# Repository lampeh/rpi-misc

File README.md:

rpi-misc
========

Raspberry Pi Gefrickel

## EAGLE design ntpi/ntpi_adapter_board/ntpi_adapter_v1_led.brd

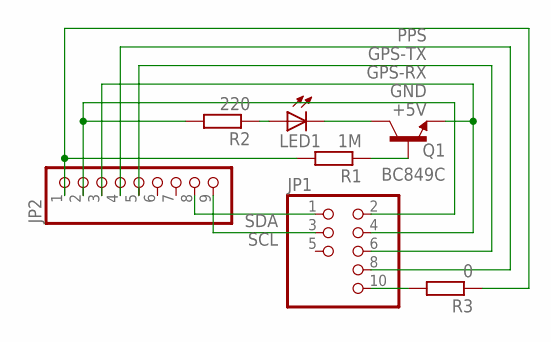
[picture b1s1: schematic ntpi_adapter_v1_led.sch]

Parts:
JP1: PINHEAD-NTPI
JP2: PINHD-1X9; 1X09
LED1: LEDCHIPLED_0805; CHIPLED_0805
Q1: BC849C; SOT23
R1: 1M; R0805W
R2: 220; R0805W
R3: 0; R0805W

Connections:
+5V: JP1.2, JP2.2, R2.2
GND: JP1.4, JP2.3, Q1.2 (E)
GPS-RX: JP1.6, JP2.5
GPS-TX: JP1.8, JP2.4
unnamed: JP1.10, R3.2
unnamed: LED1.A, R2.1
unnamed: LED1.C, Q1.3 (C)
unnamed: Q1.1 (B), R1.1
PPS: JP2.1, R1.2, R3.1
SCL: JP1.3, JP2.9
SDA: JP1.1, JP2.8

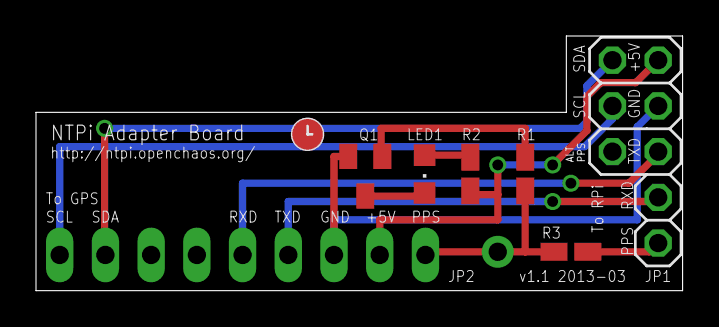
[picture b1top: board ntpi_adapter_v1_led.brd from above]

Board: 2 copper layers, 35.9 x 14.1 mm, 7 parts (1 on the bottom side), 11 nets.

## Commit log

2013-01-07 linux-rpi-pps-gpio-bcm2708.diff: register bcm2708 pps-gio device on GPIO 18 change pps_gpio_info.gpio_pin to use different GPIO pins
2013-03-08 added NTPi adapter board (Eagle 6)
2013-03-08 NTPi adapter board v1.1
2013-03-08 label SDA/SCL
2013-03-08 silk screen font changes
2013-04-12 initial import of RRD data source
2013-07-03 code adapted from https://github.com/muccc/ethersex-flipdot/blob/flipdot/hardware/flipdot/flipdot.c for Raspberry Pi / bcm2835
2013-07-03 flip_pipe: pipe 320 ASCII '1' or '0' into stdin, end with double newline
2013-07-03 don't forget bcm2835_init()
2013-07-03 added examples for flip_pipe
2013-07-07 code rewritten. now works with odd numbers of modules, too
2013-07-07 updated flip_pipe. moved examples to subdir
2013-07-07 - moved hardware specific calls to _hw_* functions. - flipped the meaning of ROW and COL enum for less or more confusion. - use uint_fast16_t instead of unsigned int. - throw preprocessor error if di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
2013-07-07 - s&r fnord fixed - display_frame doesn't pass offset to display_row
2013-07-08 working state: display_frame works update_frame yet unfinished
2013-07-08 added checker pattern
2013-07-08 example: clear screen
2013-07-08 don't wait after CLR(CLK)
2013-07-09 sreg_fill2 fills two registers in parallel
2013-07-09 /* within /* fixed
2013-07-09 use -DNOSLEEP for fastest shift clock
2013-07-10 - minor cleanup - added OE_DELAY
2013-07-10 flip dot matrix
2013-07-13 sreg_fill2 didn't push the last bit. quickfix: increase count by 1 diff code doesn't work. think again.
2013-07-13 updated flip dot matrix
2013-07-21 updated schematics
2013-07-21 driver circuit reconstruction incomplete
2013-07-21 swapped 74HC4094 QS1 / QS2
2013-07-21 updated reconstructed schematics
2013-07-21 updated matrix schematics
2013-07-26 rebuilt bitmap/frame handling - use full frames (including dummy bits) for output - no more partial-byte copy - use slow bit-wise copy to convert bitmaps to frames - added flipdot_shutdown()
2013-07-26 don't disable OE delay
2013-07-26 minor cleanup
2013-07-26 updated examples
2013-07-26 updated flipdot pixel: X-OE0 is inverted, not X-OE1
2013-07-26 Flip Dot Tester example
2013-07-26 added Makefile
2013-07-26 flipclearto[01]: should probably be built from flipclear.c
2013-07-29 flipdot video output module for VLC - threshold configuration option not used yet - display geometry still hardcoded in flipdot.h
2013-07-29 quickfix test: run flipdot_shutdown on SIGINT and SIGTERM - library problem: program execution might get aborted with OE signal still on - current flow through the matrix never stops - I don't love t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
2013-07-29 cleaned up unused code fragments
2013-07-29 removed unused module callbacks - updated Control to include fullscreen requests
2013-07-29 fixed function prototypes
2013-07-29 indentation corrected
2013-07-29 removed unused function prototypes
2013-07-29 actually, sreg_fill2 was correct and not off-by-one
2013-07-29 clean flipdot.o
2013-07-29 increased OE_DELAY
2013-07-29 added dummy vlc_keys.h
2013-07-29 install into video_output/, not misc/
2013-07-30 use full flip dot frames instead of slow bitmap
2013-10-01 code cleanup. hardcoded threshold, use adjust{brightness=xx,brightness-threshold} to control black/white ratio
2013-10-01 net names fixed: Q vs Q1, QS vs QS*
2013-10-01 update images
2013-10-01 added installation instructions
2013-10-01 fixed markup
2013-10-01 markup fixed
2013-10-04 -ffunction-sections to CFLAGS
2013-10-04 moved flipdot/ to libflipdot repository
